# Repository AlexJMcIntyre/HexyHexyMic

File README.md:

# HexyHexyMic

Because EMF needed more flashy lights!

If you're here, there's a good chance you've picked up one of my **HexyHexyMic** Hexpansions. I hope I got the chance to say hello! If not, you can find me on Mastodon: **@GlitchEngine@mastodon.social**.

HexyHexyMic adds a digital microphone to the Tildagon badge, along with a collection of audio-reactive visualisations for the badge LEDs.

This was my first attempt at building a Tildagon Hexpansion, and also my first serious dive into audio signal processing. 

The entire application is written in MicroPython and is baked into the EEPROM on the Hexpansion.

If you enjoyed this project or picked up a HexyMic at EMF2026, donations towards parts and future projects are appreciated, but never expected:

https://ko-fi.com/AlexJMcIntyre

https://paypal.me/AlexJMcIntyre

----------

## Usage

The app lives on the Hexpansion itself, so there are **no downloads or internet connection required**.

Simply plug the Hexpansion into your badge and it should launch automatically. If the badge is powered on with the Hexpansion already connected, it should load immediately during startup.

To exit the app gracefully, press the **F** button (top left).

Removing the Hexpansion should also exit automatically. If your LEDs don't return afterwards, try toggling them back on from the badge menu or simply reboop the badge.

### Controls

-   **Up / Down**: Navigate the menu
-   **C** (bottom right): Select an option
-   **F** (top left): Exit the application

----------

## Visualisation Modes

### RMS (default)

Uses the **Root Mean Square** of the incoming audio as a measure of volume.

The louder the sound, the more LEDs illuminate.

### Zero Crossing (ZC)

Counts how often the audio waveform crosses zero to estimate its average pitch.

It's a very lightweight algorithm that gives surprisingly fun results despite being only a rough approximation.

### FFT

Performs a tiny **Fast Fourier Transform** to estimate the energy in twelve frequency bands.

This isn't intended to be an accurate spectrum analyser, but it's fast enough to run smoothly on the badge and gives a satisfying visual representation of the music.

### Vortex

Attempts to detect the beat of whatever it's listening to and synchronise a rotating comet of light with the rhythm.

It's definitely more artistic than scientific, but I think it looks rather nice.

----------

## Beat Flash

When enabled, the app attempts to detect musical beats from the incoming audio. Whenever it thinks it has found one, the LEDs briefly desaturate to create a bright flash effect.

Beat detection is intentionally simple, so don't expect perfect DJ-grade synchronisation. It works best with music that has a clear, steady rhythm.

----------

## Automatic Volume Calibration

The visualisers automatically adapt to the ambient sound level.

This means they work just as well in a quiet workshop as they do in a noisy concert.

If you make an unusually loud noise (for example by tapping the microphone), the display may become less sensitive for a few seconds while it recalibrates itself.

----------

## Compatibility

Tested with **Tildagon firmware 1.10**.

----------

## Hacking on HexyHexyMic

The source is included in this repository, but unlike a normal Python application it isn't installed directly onto the badge.

The app is flashed onto the Hexpansion's EEPROM, allowing it to run automatically whenever the Hexpansion is plugged into a Tildagon.

To build or modify the app you'll currently need:

- A checkout of the Tildagon firmware repository
- This project's source files
- A way of flashing the EEPROM on the Hexpansion

I've included the batch files I use to build and flash the EEPROM image as a starting point. They're fairly simple, but you'll need to adjust the paths for your own setup.

If you improve the code or add new visualisation modes, I'd love to hear about it!

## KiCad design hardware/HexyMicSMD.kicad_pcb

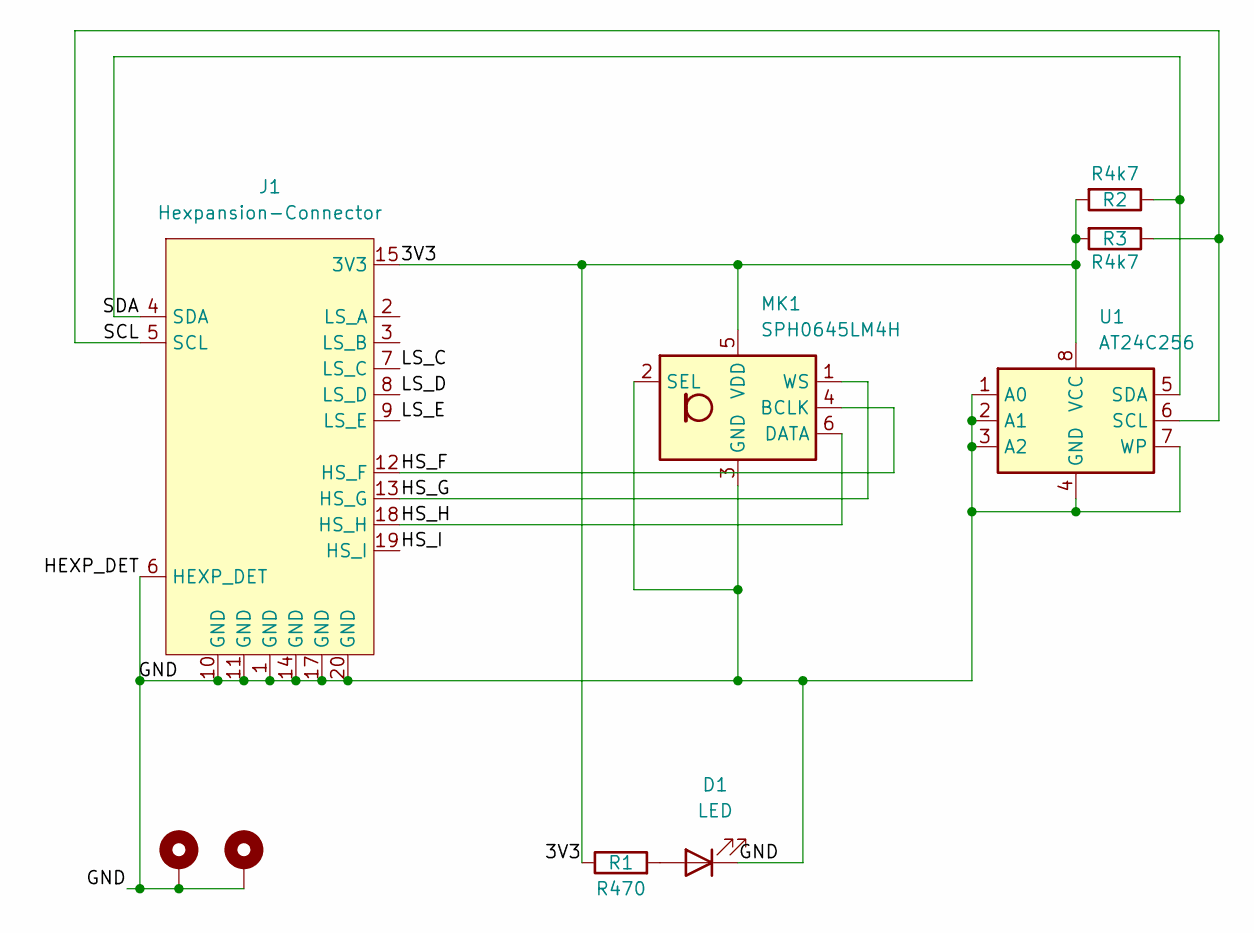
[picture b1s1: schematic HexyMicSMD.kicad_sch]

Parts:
D1: LED; LED_0603_1608Metric; LCSC C2286
H1: MountingHole_Pad; MountingHole_2.2mm_M2_Pad_Via; LCSC 0
H2: MountingHole_Pad; MountingHole_2.2mm_M2_Pad_Via
J1: Hexpansion-Connector; hexpansion-edge-connector
MK1: SPH0645LM4H; Knowles_SPH0645LM4H-6_3.5x2.65mm; LCSC C19272537
R1: R470; R_0603_1608Metric; LCSC C23179
R2, R3: R4k7; R_0603_1608Metric; LCSC C21190
U1: AT24C256; SOIC-8_3.9x4.9mm_P1.27mm; LCSC C19723712

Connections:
/3V3: J1.15 (3V3), J1.16 (3V3), MK1.5 (VDD), R1.1, R2.2, R3.2, U1.8 (VCC)
/GND: D1.1 (K), H1.1, H2.1, J1.1 (GND), J1.6 (HEXP_DET), J1.10 (GND), J1.11 (GND), J1.14 (GND), J1.17 (GND), J1.20 (GND), MK1.2 (SEL), MK1.3 (GND), U1.1 (A0), U1.2 (A1), U1.3 (A2), U1.4 (GND), U1.7 (WP)
/HS_F: J1.12 (HS_F), MK1.4 (BCLK)
/HS_G: J1.13 (HS_G), MK1.1 (WS)
/HS_H: J1.18 (HS_H), MK1.6 (DATA)
/HS_I: J1.19 (HS_I)
/LS_C: J1.7 (LS_C)
/LS_D: J1.8 (LS_D)
/LS_E: J1.9 (LS_E)
/SCL: J1.5 (SCL), R3.1, U1.6 (SCL)
/SDA: J1.4 (SDA), R2.1, U1.5 (SDA)
unnamed: D1.2 (A), R1.2

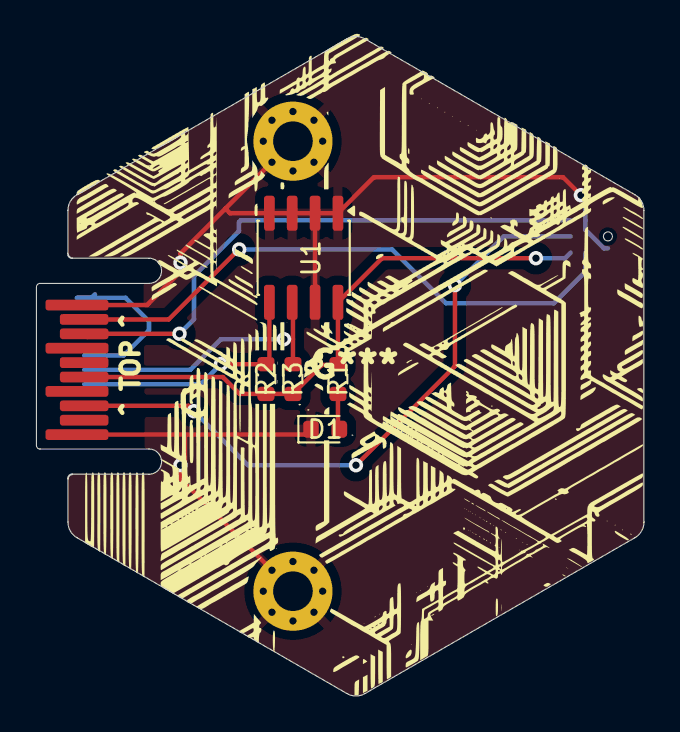
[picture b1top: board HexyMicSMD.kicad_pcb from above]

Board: 2 copper layers, 33.7 x 36.6 mm, 9 parts (1 on the bottom side), 8 nets.

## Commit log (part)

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2025-06-23 Create V0_1.py
    Proof of concept microphone reading
2025-06-24 Create v0_2.py, LED proof of concept
2025-06-24 visualisation tests
2025-06-24 vis tweaks
2025-06-24 Update v0_3.py, demo vis created
2025-06-29 hexpansion port detection
2025-06-30 EEPROM app loading
2026-04-08 Refactor MicApp to include menu and audio features
2026-04-08 Update flash.bat to copy app.py from new location
2026-04-08 Add script to prepare EEPROM using mpremote
2026-04-10 Refactor MicApp to include FFT visualization
2026-04-10 Refactor MicApp and update menu items
2026-04-10 Enhance MicApp with brightness control and beat detection
    Refactor MicApp to include brightness control and beat detection features.
2026-04-15 Add Vortex visual mode and optimize audio methods
    Refactor MicApp to include a new visual mode 'Vortex' and optimize audio processing methods.
